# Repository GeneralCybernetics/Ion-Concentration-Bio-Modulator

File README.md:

# Ion Concentration Biomodulator (v4)

The purpose of the chip is to enable an incubator to dispense ions over a cellular culture within the incubator.

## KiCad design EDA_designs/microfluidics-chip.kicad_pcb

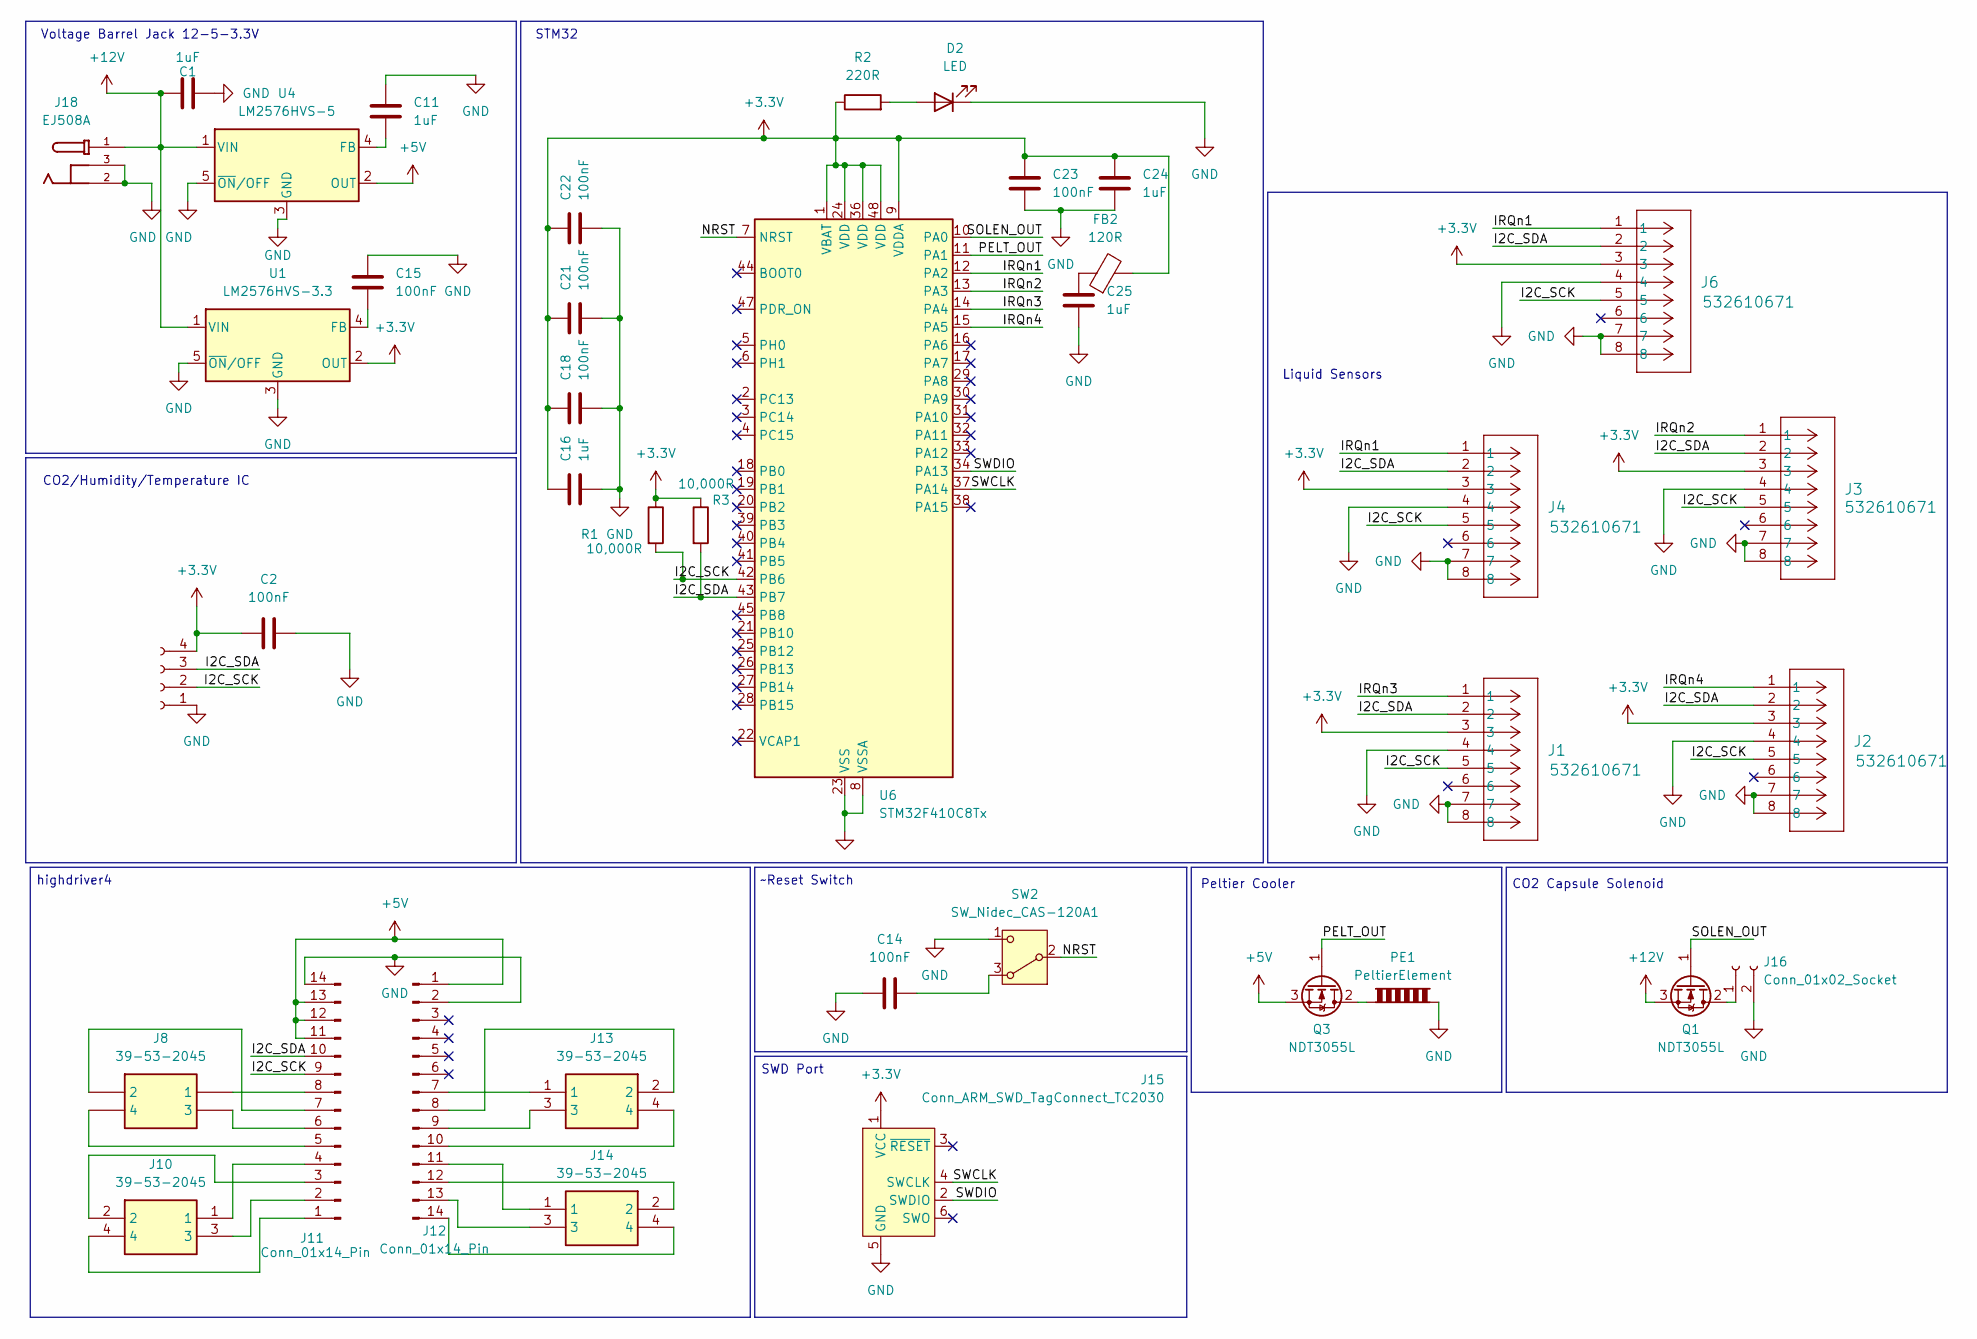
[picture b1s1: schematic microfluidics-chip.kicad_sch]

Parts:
C1, C11, C16, C24, C25: 1uF; C_0402_1005Metric
C2, C14, C15, C18, C21, C22, C23: 100nF; C_0402_1005Metric
D2: LED; LED_D3.0mm
FB2: 120R; L_0603_1608Metric
J1, J2, J3, J4, J6: 532610671; CON_532610671
J5: Conn_01x04_Socket; PinSocket_1x04_P2.54mm_Vertical
J8, J10, J13, J14: 39-53-2045; 39532045; Mouser Part Number 538-39532045
J11, J12: Conn_01x14_Pin; PinSocket_1x14_P2.54mm_Vertical
J15: Conn_ARM_SWD_TagConnect_TC2030; Tag-Connect_TC2030-IDC-FP_2x03_P1.27mm_Vertical
J16: Conn_01x02_Socket; PinSocket_1x02_P2.54mm_Vertical
J18: EJ508A; MPD_EJ508A; PARTREV J
PE1: PeltierElement; PinSocket_1x02_P2.54mm_Vertical
Q1, Q3: NDT3055L; SOT-223-3_TabPin2
R1, R3: 10,000R; R_Axial_DIN0207_L6.3mm_D2.5mm_P7.62mm_Horizontal
R2: 220R; R_Axial_DIN0204_L3.6mm_D1.6mm_P5.08mm_Horizontal
SW2: SW_Nidec_CAS-120A1; Nidec_Copal_CAS-120A
U1: LM2576HVS-3.3; TO-263-5_TabPin3
U4: LM2576HVS-5; TO-263-5_TabPin3
U6: STM32F410C8Tx; LQFP-48_7x7mm_P0.5mm

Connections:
+3.3V: C2.1, C16.1, C18.1, C21.1, C22.1, C23.1, C24.1, FB2.2, J1.3, J2.3, J3.3, J4.3, J5.4, J6.3, J15.1 (VCC), R1.1, R2.1, R3.1, U1.2 (OUT), U6.1 (VBAT), U6.9 (VDDA), U6.24 (VDD), U6.36 (VDD), U6.48 (VDD)
+5V: J11.11, J11.12, J11.13, J12.1, Q3.3 (S), U4.2 (OUT)
+12V: C1.1, J18.1, Q1.3 (S), U1.1 (VIN), U4.1 (VIN)
/I2C_SCK: J1.5, J2.5, J3.5, J4.5, J5.2, J6.5, J11.9, R1.2, U6.42 (PB6)
/I2C_SDA: J1.2, J2.2, J3.2, J4.2, J5.3, J6.2, J11.10, R3.2, U6.43 (PB7)
/IRQn1: J4.1, J6.1, U6.12 (PA2)
/IRQn2: J3.1, U6.13 (PA3)
/IRQn3: J1.1, U6.14 (PA4)
/IRQn4: J2.1, U6.15 (PA5)
/NRST: SW2.2 (B), U6.7 (NRST)
/PELT_OUT: Q3.1 (G), U6.11 (PA1)
/SOLEN_OUT: Q1.1 (G), U6.10 (PA0)
/SWCLK: J15.4 (SWCLK), U6.37 (PA14)
/SWDIO: J15.2 (SWDIO), U6.34 (PA13)
GND: C1.2, C2.2, C11.1, C14.1, C15.1, C16.2, C18.2, C21.2, C22.2, C23.2, C24.2, C25.2, D2.1 (K), J1.4, J1.7, J1.8, J2.4, J2.7, J2.8, J3.4, J3.7, J3.8, J4.4, J4.7, J4.8, J5.1, J6.4, J6.7, J6.8, J11.14, J12.2, J15.5 (GND), J16.2, J18.2, J18.3, PE1.2, SW2.1 (C), U1.3 (GND), U1.5 (~ON/OFF), U4.3 (GND), U4.5 (~ON/OFF), U6.8 (VSSA), U6.23 (VSS), U6.35 (VSS), U6.46 (VSS)
unnamed: C25.1, FB2.1
unnamed: D2.2 (A), R2.2
unnamed: J10.4, J11.1
unnamed: J10.3, J11.2
unnamed: J10.2, J11.3
unnamed: J10.1, J11.4
unnamed: J8.4, J11.5
unnamed: J8.3, J11.6
unnamed: J8.2, J11.7
unnamed: J8.1, J11.8
unnamed: J12.7, J13.1
unnamed: J12.8, J13.2
unnamed: J12.9, J13.3
unnamed: J12.10, J13.4
unnamed: J12.11, J14.1
unnamed: J12.12, J14.2
unnamed: J12.13, J14.3
unnamed: J12.14, J14.4
unnamed: J16.1, Q1.2 (D)
unnamed: PE1.1, Q3.2 (D)
unnamed: C14.2, SW2.3 (A)
unnamed: C15.2, U1.4 (FB)
unnamed: C11.2, U4.4 (FB)

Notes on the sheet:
Voltage Barrel Jack 12-5-3.3V
CO2/Humidity/Temperature IC
Peltier Cooler
STM32
SWD Port
Liquid Sensors
highdriver4
~Reset Switch
CO2 Capsule Solenoid

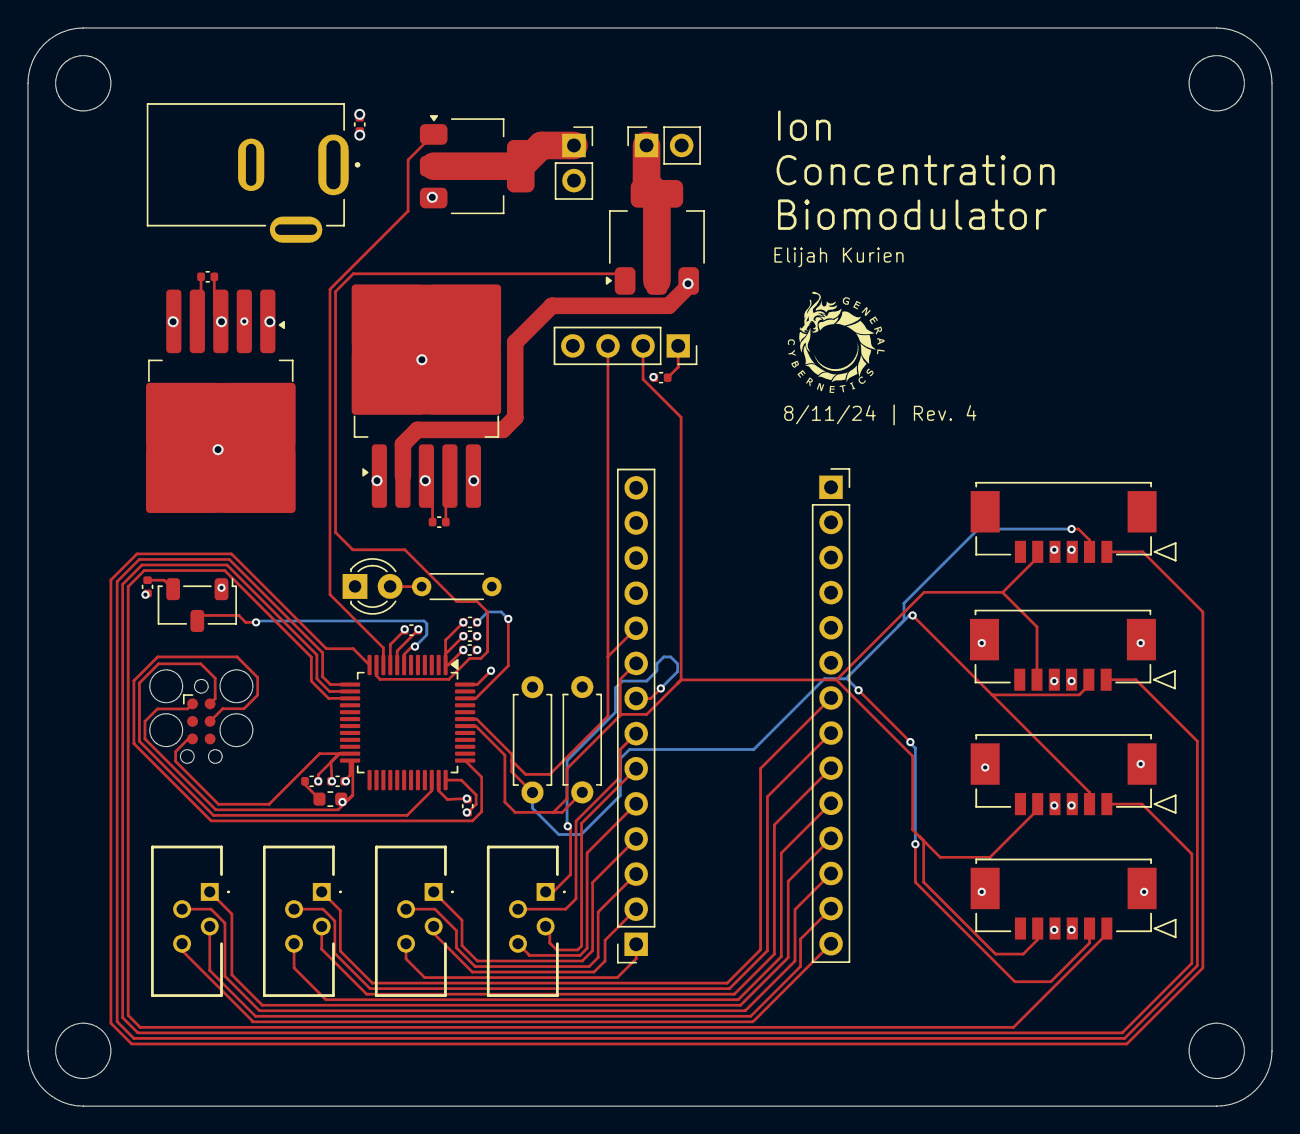
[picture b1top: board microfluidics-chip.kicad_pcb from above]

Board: 4 copper layers, 90.0 x 78.0 mm, 38 parts (0 on the bottom side), 38 nets.

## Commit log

2024-08-11 Pushing v2
2024-08-12 Pushing v3
2024-08-12 Update README.md (v3)
2024-08-12 pushing v5
